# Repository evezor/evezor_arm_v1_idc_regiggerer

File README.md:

# evezor_arm_v1_idc_regiggerer

This boards incorporates two gadgeteer ports intended to work with the other devices in this ecosystem. 
I originally created this board as a way to remap pins. And using this thing I decided that I hated everything about systems like the gadgeteer standard, pmod, shields, hats, and many of the other systems that intend to create a reusable set of standards among controllers and devices. But inevitably you run into issues like, this pin does not have pwm and I want it to. Or this pin does not have pullups or can only be used as an input and on and on. 
Secondly, when you end up going through these mappings your code and schematics begin to look just as ugly and trying to trace down issues when you want to change or diagnose things you must again untangle all these mappings. 
No more! I threw all these boards in the trash and have no intention of looking back.  
It's a noble goal to try and create some kind of standards for breaking out pins and I will continue to create and use them, but attempting to have a paradigm like this as the foundation is untenable and was part of the inspiration for the larger Evezor edge board concept. 

Source files for  this board can be found here:  https://github.com/evezor/evezor_arm_v1_idc_regiggerer

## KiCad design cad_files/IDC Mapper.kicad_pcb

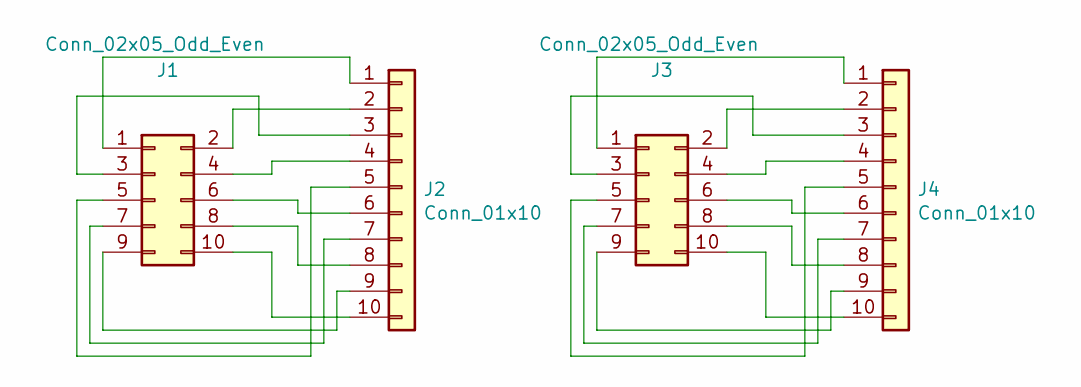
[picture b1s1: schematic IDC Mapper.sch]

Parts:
J1, J3: Conn_02x05_Odd_Even; IDC-Header_2x05_P2.54mm_Vertical
J2, J4: Conn_01x10; PinHeader_1x10_P2.54mm_Vertical

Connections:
unnamed: J1.1, J2.1
unnamed: J1.2, J2.2
unnamed: J1.3, J2.3
unnamed: J1.4, J2.4
unnamed: J1.5, J2.5
unnamed: J1.6, J2.6
unnamed: J1.7, J2.7
unnamed: J1.8, J2.8
unnamed: J1.9, J2.9
unnamed: J1.10, J2.10
unnamed: J3.1, J4.1
unnamed: J3.2, J4.2
unnamed: J3.3, J4.3
unnamed: J3.4, J4.4
unnamed: J3.5, J4.5
unnamed: J3.6, J4.6
unnamed: J3.7, J4.7
unnamed: J3.8, J4.8
unnamed: J3.9, J4.9
unnamed: J3.10, J4.10

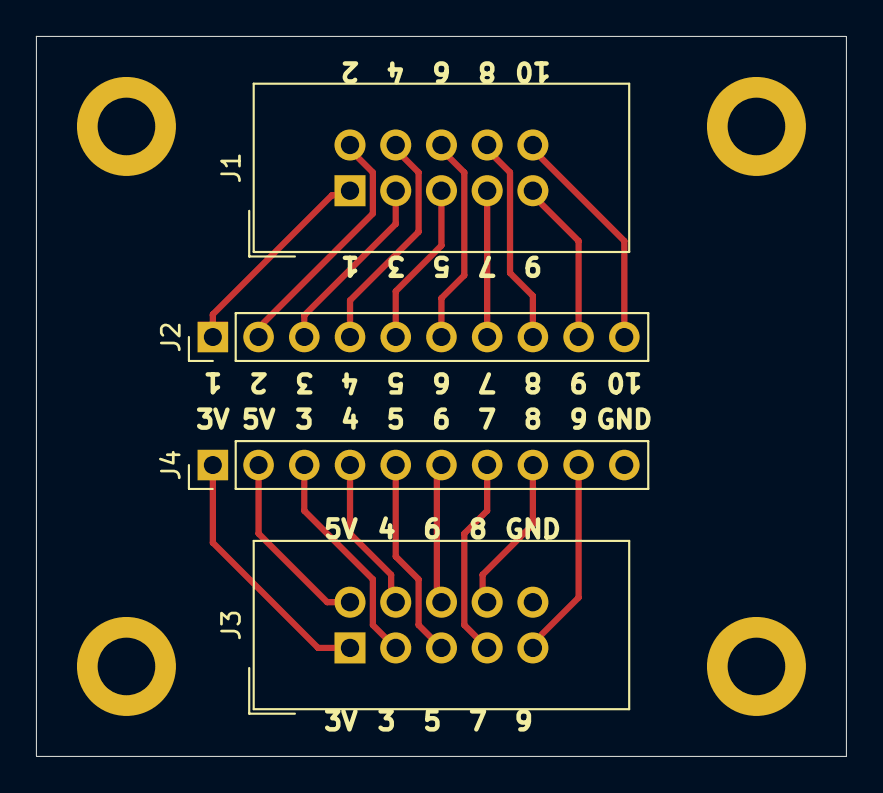
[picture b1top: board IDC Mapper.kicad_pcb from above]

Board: 2 copper layers, 45.0 x 40.0 mm, 4 parts (0 on the bottom side), 20 nets.

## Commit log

2023-10-12 init
